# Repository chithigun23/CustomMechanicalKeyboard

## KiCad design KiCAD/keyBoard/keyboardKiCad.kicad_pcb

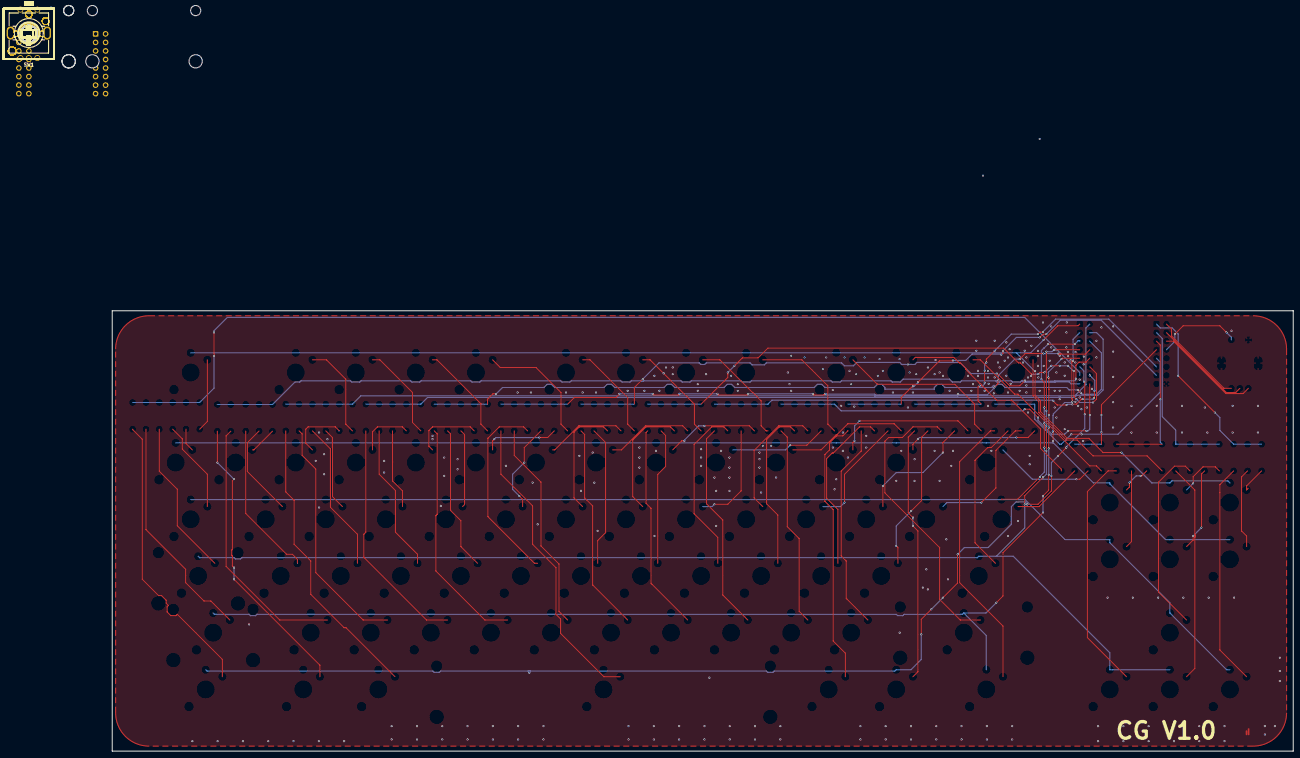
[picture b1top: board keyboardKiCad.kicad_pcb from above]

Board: 2 copper layers, 354.0 x 132.0 mm, 172 parts (0 on the bottom side), 111 nets.

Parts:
CNN1: keyboardMCU_Connector
D1, D2, D3, D4, D5, D6, D7, D8, D9, D10, D11, D12, D13, D14, D15, D16, D17, D18, D19, D20, D21, D22, D23, D24, D25, D26, D27, D28, D29, D30, D31, D32, D33, D34, D35, D36, D37, D38, D39, D40, D41, D42, D43, D44, D45, D46, D47, D48, D49, D50, D51, D52, D53, D54, D55, D56, D57, D58, D59, D60, D61, D62, D63, D64, D66, D67, D68, D69, D70, D71, D72, D73, D74, D75, D76, D77, D78, D79, D80, D81, D82, D83, D84: DO-35_BD2.0-L4.0-P8.00-D0.5-FD
H1, H4: Stabilizer_Cherry_MX_2.00u
H7: Stabilizer_Cherry_MX_3.00u
H8: Stabilizer_Cherry_MX_6.25u
S1, S3, S72: SW_Kailh_Choc_V2_1.50u
S2, S7, S8, S9, S10, S12, S13, S14, S15, S16, S18, S19, S20, S21, S22, S23, S24, S25, S26, S27, S28, S29, S30, S31, S32, S34, S35, S36, S37, S38, S39, S40, S41, S42, S43, S44, S45, S46, S47, S48, S49, S50, S51, S52, S53, S54, S55, S56, S57, S59, S60, S61, S62, S64, S65, S66, S67, S70, S73, S74, S75, S76, S77, S78, S79, S80, S81, S82, S83: SW_Kailh_Choc_V2_1.00u
S4: SW_Kailh_Choc_V2_1.75u
S5, S68: SW_Kailh_Choc_V2_2.25u
S6, S69, S71: SW_Kailh_Choc_V2_2.00u
S11, S17, S58: SW_Kailh_Choc_V2_1.25u
S33: SW_Kailh_Choc_V2_6.25u
S63: SW_Kailh_Choc_V2_2.75u
SW1: RotaryEncoder_Switch_MP; SW-TH_EC11XXXXXXXX

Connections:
COL1: CNN1.7, D1.1 (K), D2.1 (K), D3.1 (K), D4.1 (K), D5.1 (K), D6.1 (K)
COL2: CNN1.8, D7.1 (K), D8.1 (K), D9.1 (K), D10.1 (K), D11.1 (K)
COL3: CNN1.9, D12.1 (K), D13.1 (K), D14.1 (K), D15.1 (K), D16.1 (K), D17.1 (K)
COL4: CNN1.10, D18.1 (K), D19.1 (K), D20.1 (K), D21.1 (K), D22.1 (K)
COL5: CNN1.11, D23.1 (K), D24.1 (K), D25.1 (K), D26.1 (K), D27.1 (K)
COL6: CNN1.12, D28.1 (K), D29.1 (K), D30.1 (K), D31.1 (K), D32.1 (K), D33.1 (K)
COL7: CNN1.13, D34.1 (K), D35.1 (K), D36.1 (K), D37.1 (K), D38.1 (K)
COL8: CNN1.14, D39.1 (K), D40.1 (K), D41.1 (K), D42.1 (K), D43.1 (K)
COL9: CNN1.15, D44.1 (K), D45.1 (K), D46.1 (K), D47.1 (K), D48.1 (K)
COL10: CNN1.16, D49.1 (K), D50.1 (K), D51.1 (K), D52.1 (K), D53.1 (K)
COL11: CNN1.23, D54.1 (K), D55.1 (K), D56.1 (K), D57.1 (K), D58.1 (K)
COL12: CNN1.22, D59.1 (K), D60.1 (K), D61.1 (K), D62.1 (K), D63.1 (K), D64.1 (K)
COL13: CNN1.21, D66.1 (K), D67.1 (K), D68.1 (K), D69.1 (K), D70.1 (K)
COL14: CNN1.20, D71.1 (K), D72.1 (K), D73.1 (K)
COL15: CNN1.19, D74.1 (K), D75.1 (K), D76.1 (K), D77.1 (K)
COL16: CNN1.18, D78.1 (K), D79.1 (K), D80.1 (K), D81.1 (K)
COL17: CNN1.17, D82.1 (K), D83.1 (K), D84.1 (K)
GND: CNN1.32, SW1.6, SW1.7, SW1.E
unnamed: D1.2 (A), S1.2
unnamed: D2.2 (A), S2.2
unnamed: D3.2 (A), S3.2
unnamed: D4.2 (A), S4.2
unnamed: D5.2 (A), S5.2
unnamed: D6.2 (A), S6.2
unnamed: D7.2 (A), S7.2
unnamed: D8.2 (A), S8.2
unnamed: D9.2 (A), S9.2
unnamed: D10.2 (A), S10.2
unnamed: D11.2 (A), S11.2
unnamed: D12.2 (A), S12.2
unnamed: D13.2 (A), S13.2
unnamed: D14.2 (A), S14.2
unnamed: D15.2 (A), S15.2
unnamed: D16.2 (A), S16.2
unnamed: D17.2 (A), S17.2
unnamed: D18.2 (A), S18.2
unnamed: D19.2 (A), S19.2
unnamed: D20.2 (A), S20.2
unnamed: D21.2 (A), S21.2
unnamed: D22.2 (A), S22.2
unnamed: D23.2 (A), S23.2
unnamed: D24.2 (A), S24.2
unnamed: D25.2 (A), S25.2
unnamed: D26.2 (A), S26.2
unnamed: D27.2 (A), S27.2
unnamed: D28.2 (A), S28.2
unnamed: D29.2 (A), S29.2
unnamed: D30.2 (A), S30.2
unnamed: D31.2 (A), S31.2
unnamed: D32.2 (A), S32.2
unnamed: D33.2 (A), S33.2
unnamed: D34.2 (A), S34.2
unnamed: D35.2 (A), S35.2
unnamed: D36.2 (A), S36.2
unnamed: D37.2 (A), S37.2
unnamed: D38.2 (A), S38.2
unnamed: D39.2 (A), S39.2
unnamed: D40.2 (A), S40.2
unnamed: D41.2 (A), S41.2
unnamed: D42.2 (A), S42.2
unnamed: D43.2 (A), S43.2
unnamed: D44.2 (A), S44.2
unnamed: D45.2 (A), S45.2
unnamed: D46.2 (A), S46.2
unnamed: D47.2 (A), S47.2
unnamed: D48.2 (A), S48.2
unnamed: D49.2 (A), S49.2
unnamed: D50.2 (A), S50.2
unnamed: D51.2 (A), S51.2
unnamed: D52.2 (A), S52.2
unnamed: D53.2 (A), S53.2
unnamed: D54.2 (A), S54.2
unnamed: D55.2 (A), S55.2
unnamed: D56.2 (A), S56.2
unnamed: D57.2 (A), S57.2
unnamed: D58.2 (A), S58.2
unnamed: D59.2 (A), S59.2
unnamed: D60.2 (A), S60.2
unnamed: D61.2 (A), S61.2
unnamed: D62.2 (A), S62.2
unnamed: D63.2 (A), S63.2
unnamed: D64.2 (A), S64.2
unnamed: D66.2 (A), S65.2
unnamed: D67.2 (A), S66.2
unnamed: D68.2 (A), S67.2
unnamed: D69.2 (A), S68.2
unnamed: D70.2 (A), S69.2
unnamed: D71.2 (A), S70.2
unnamed: D72.2 (A), S71.2
unnamed: D73.2 (A), S72.2
unnamed: D74.2 (A), S73.2
unnamed: D75.2 (A), S74.2
unnamed: D76.2 (A), S75.2
unnamed: D77.2 (A), S76.2
unnamed: D78.2 (A), S77.2
unnamed: D79.2 (A), S78.2
unnamed: D80.2 (A), S79.2
unnamed: D81.2 (A), S80.2
unnamed: D82.2 (A), S81.2
unnamed: D83.2 (A), S82.2
unnamed: D84.2 (A), S83.2
ROW1: CNN1.1, S1.1, S12.1, S18.1, S23.1, S28.1, S34.1, S39.1, S44.1, S49.1, S59.1, S65.1, S70.1, S73.1, S77.1, S81.1
ROW2: CNN1.2, S2.1, S7.1, S13.1, S19.1, S24.1, S29.1, S35.1, S40.1, S45.1, S50.1, S54.1, S60.1, S66.1, S71.1, S74.1, S78.1, S82.1
ROW3: CNN1.3, S3.1, S8.1, S14.1, S20.1, S25.1, S30.1, S36.1, S41.1, S46.1, S51.1, S55.1, S61.1, S67.1, S72.1, S75.1, S79.1, S83.1
ROW4: CNN1.4, S4.1, S9.1, S15.1, S21.1, S26.1, S31.1, S37.1, S42.1, S47.1, S52.1, S56.1, S62.1, S68.1, S76.1, S80.1
ROW5: CNN1.5, S5.1, S10.1, S16.1, S22.1, S27.1, S32.1, S38.1, S43.1, S48.1, S53.1, S57.1, S63.1, S69.1
ROW6: CNN1.6, S6.1, S11.1, S17.1, S33.1, S58.1, S64.1
rotA: CNN1.25, SW1.A
rotB: CNN1.27, SW1.B
rotC: CNN1.26, SW1.C
rotSW: CNN1.28, SW1.D

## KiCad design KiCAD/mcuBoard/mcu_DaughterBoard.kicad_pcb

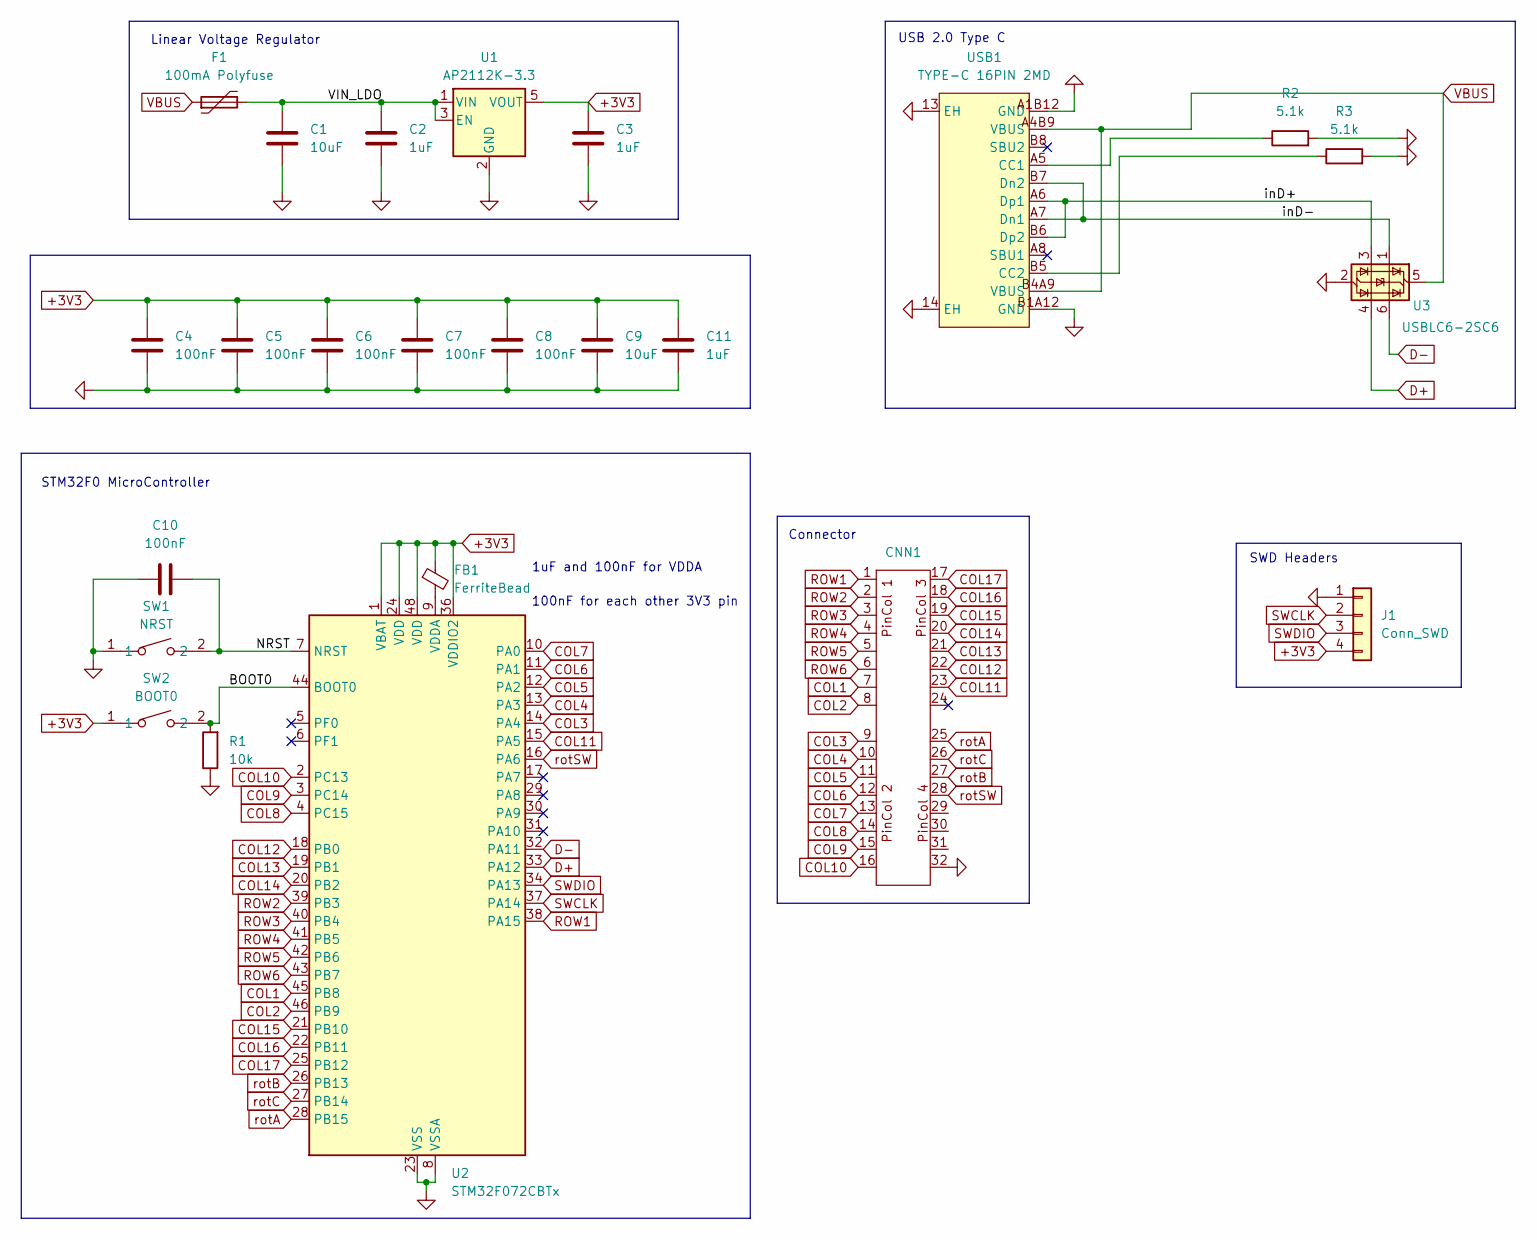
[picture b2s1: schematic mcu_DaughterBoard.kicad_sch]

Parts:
C1, C9: 10uF; C_0402_1005Metric_Pad0.74x0.62mm_HandSolder
C2, C3, C11: 1uF; C_0402_1005Metric_Pad0.74x0.62mm_HandSolder
C4, C5, C6, C7, C8, C10: 100nF; C_0402_1005Metric_Pad0.74x0.62mm_HandSolder
CNN1: keyboardMCU_Connector
F1: 100mA Polyfuse; C_0603_1608Metric_Pad1.08x0.95mm_HandSolder
FB1: FerriteBead; C_0603_1608Metric_Pad1.08x0.95mm_HandSolder
J1: Conn_SWD; PinHeader_1x04_P2.54mm_Vertical
R1: 10k; R_0402_1005Metric_Pad0.72x0.64mm_HandSolder
R2, R3: 5.1k; R_0402_1005Metric_Pad0.72x0.64mm_HandSolder
SW1: NRST; SW-SMD_L3.9-W3.0-P4.45; MPN TS-1088-AR02016; LCSC Part C720477
SW2: BOOT0; SW-SMD_L3.9-W3.0-P4.45; MPN TS-1088-AR02016; LCSC Part C720477
U1: AP2112K-3.3; SOT-23-5
U2: STM32F072CBTx; LQFP-48_7x7mm_P0.5mm
U3: USBLC6-2SC6; SOT-23-6
USB1: TYPE-C 16PIN 2MD; USB-C-SMD_TYPE-C-16PIN-2MD-073; MPN TYPE-C 16PIN 2MD(073); LCSC Part C2765186

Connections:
+3V3: C3.1, C4.2, C5.2, C6.2, C7.2, C8.2, C9.2, C11.1, FB1.1, J1.4, SW2.1, U1.5 (VOUT), U2.1 (VBAT), U2.24 (VDD), U2.36 (VDDIO2), U2.48 (VDD)
/BOOT0: R1.2, SW2.2, U2.44 (BOOT0)
/NRST: C10.2, SW1.2, U2.7 (NRST)
/VIN_LDO: C1.2, C2.1, F1.2, U1.1 (VIN), U1.3 (EN)
/inD+: U3.3 (I/O2), USB1.A6 (Dp1), USB1.B6 (Dp2)
/inD-: U3.1 (I/O1), USB1.A7 (Dn1), USB1.B7 (Dn2)
COL1: CNN1.7, U2.45 (PB8)
COL2: CNN1.8, U2.46 (PB9)
COL3: CNN1.9, U2.14 (PA4)
COL4: CNN1.10, U2.13 (PA3)
COL5: CNN1.11, U2.12 (PA2)
COL6: CNN1.12, U2.11 (PA1)
COL7: CNN1.13, U2.10 (PA0)
COL8: CNN1.14, U2.4 (PC15)
COL9: CNN1.15, U2.3 (PC14)
COL10: CNN1.16, U2.2 (PC13)
COL11: CNN1.23, U2.15 (PA5)
COL12: CNN1.22, U2.18 (PB0)
COL13: CNN1.21, U2.19 (PB1)
COL14: CNN1.20, U2.20 (PB2)
COL15: CNN1.19, U2.21 (PB10)
COL16: CNN1.18, U2.22 (PB11)
COL17: CNN1.17, U2.25 (PB12)
D+: U2.33 (PA12), U3.4 (I/O2)
D-: U2.32 (PA11), U3.6 (I/O1)
GND: C1.1, C2.2, C3.2, C4.1, C5.1, C6.1, C7.1, C8.1, C9.1, C10.1, C11.2, CNN1.32, J1.1, R1.1, R2.2, R3.2, SW1.1, U1.2 (GND), U2.8 (VSSA), U2.23 (VSS), U2.35 (VSS), U2.47 (VSS), U3.2 (GND), USB1.13 (EH), USB1.14 (EH), USB1.A1B12 (GND), USB1.B1A12 (GND)
unnamed: FB1.2, U2.9 (VDDA)
unnamed: R2.1, USB1.A5 (CC1)
unnamed: R3.1, USB1.B5 (CC2)
ROW1: CNN1.1, U2.38 (PA15)
ROW2: CNN1.2, U2.39 (PB3)
ROW3: CNN1.3, U2.40 (PB4)
ROW4: CNN1.4, U2.41 (PB5)
ROW5: CNN1.5, U2.42 (PB6)
ROW6: CNN1.6, U2.43 (PB7)
SWCLK: J1.2, U2.37 (PA14)
SWDIO: J1.3, U2.34 (PA13)
VBUS: F1.1, U3.5 (VBUS), USB1.A4B9 (VBUS), USB1.B4A9 (VBUS)
rotA: CNN1.25, U2.28 (PB15)
rotB: CNN1.27, U2.26 (PB13)
rotC: CNN1.26, U2.27 (PB14)
rotSW: CNN1.28, U2.16 (PA6)

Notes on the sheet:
1uF and 100nF for VDDA
SWD Headers
USB 2.0 Type C
Linear Voltage Regulator
100nF for each other 3V3 pin
Connector
STM32F0 MicroController

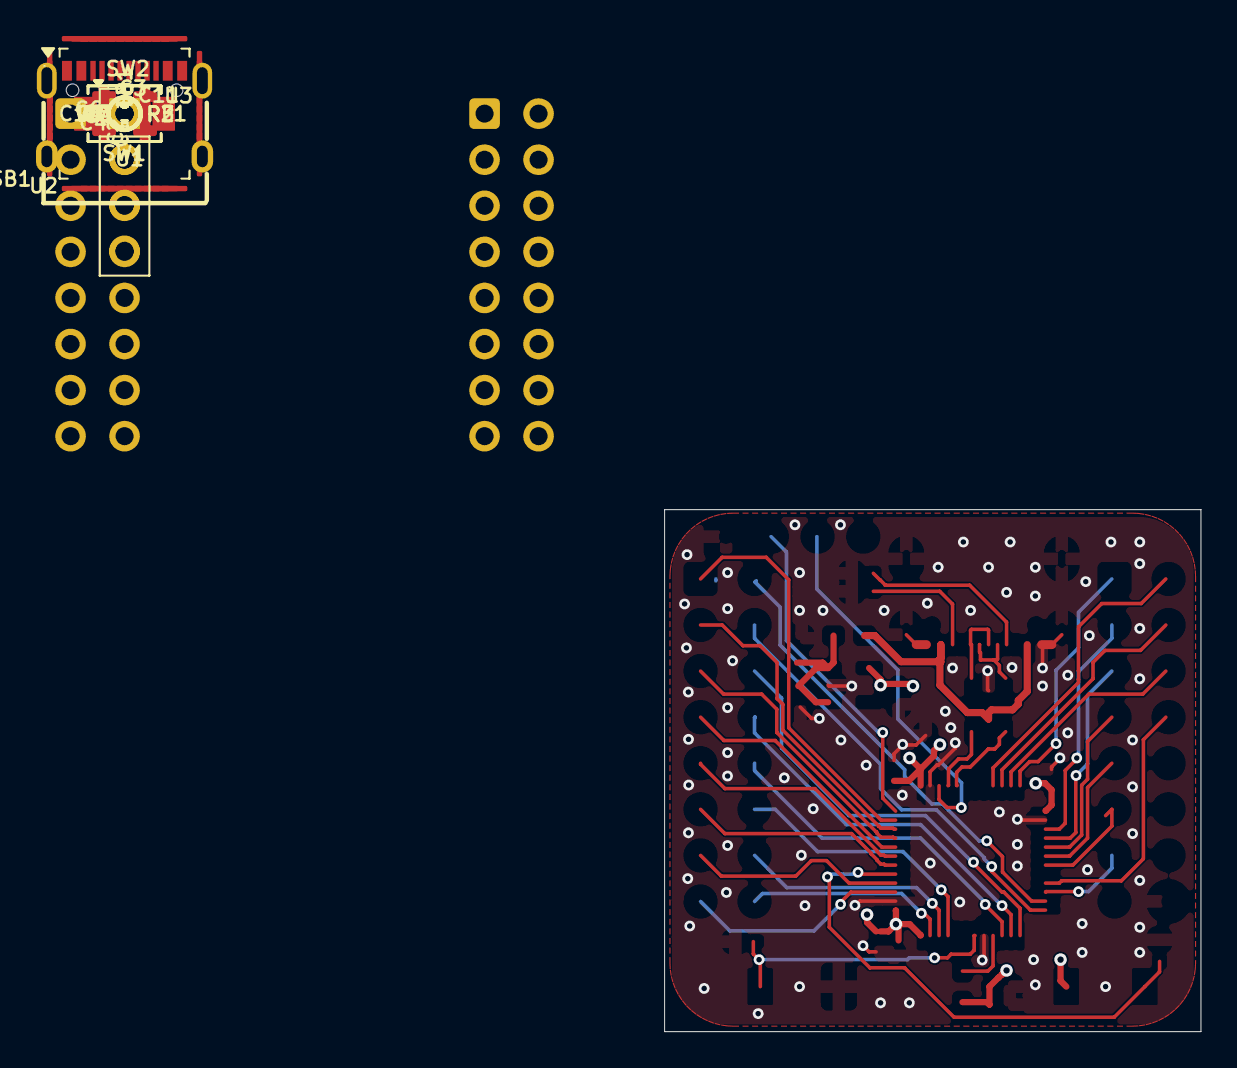
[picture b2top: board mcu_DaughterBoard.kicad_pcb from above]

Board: 4 copper layers, 29.8 x 29.0 mm, 24 parts (0 on the bottom side), 42 nets.
